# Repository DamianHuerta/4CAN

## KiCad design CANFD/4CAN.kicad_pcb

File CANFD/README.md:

# 4CAN-FD Design Files

-----------------------------------------------------------------------------------

## Note: Upon opening the project in KiCad, there may be some warnings.Click through the warnings to view the PCB as inteded.

------------------------------------------------------------------------------------

The files present in this repo are the project files used with the update of 4CAN to support CAN-FD protocol. For details on updated hardware view the Bill of Materials. All parts are available on digikey.

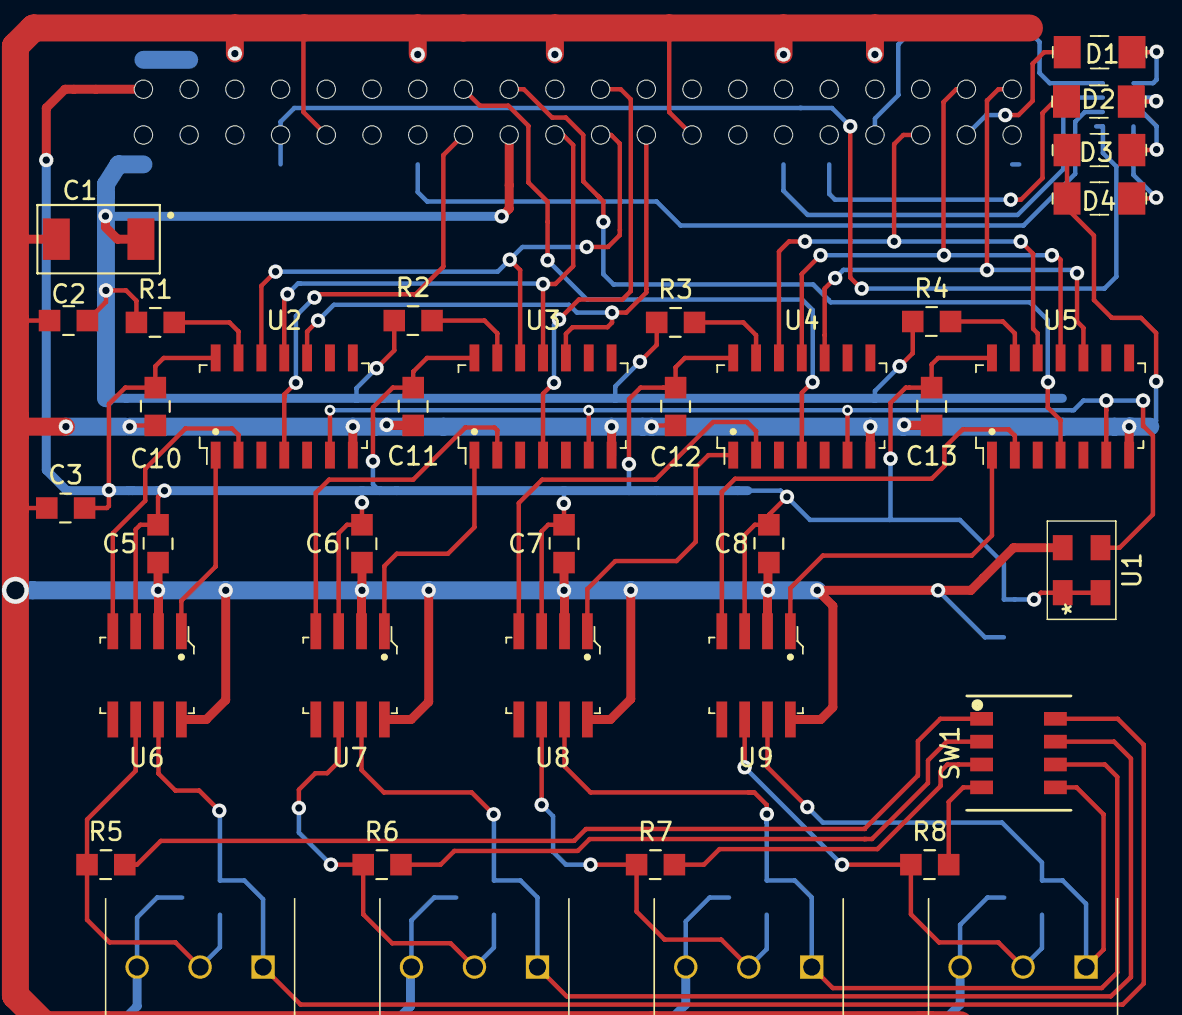
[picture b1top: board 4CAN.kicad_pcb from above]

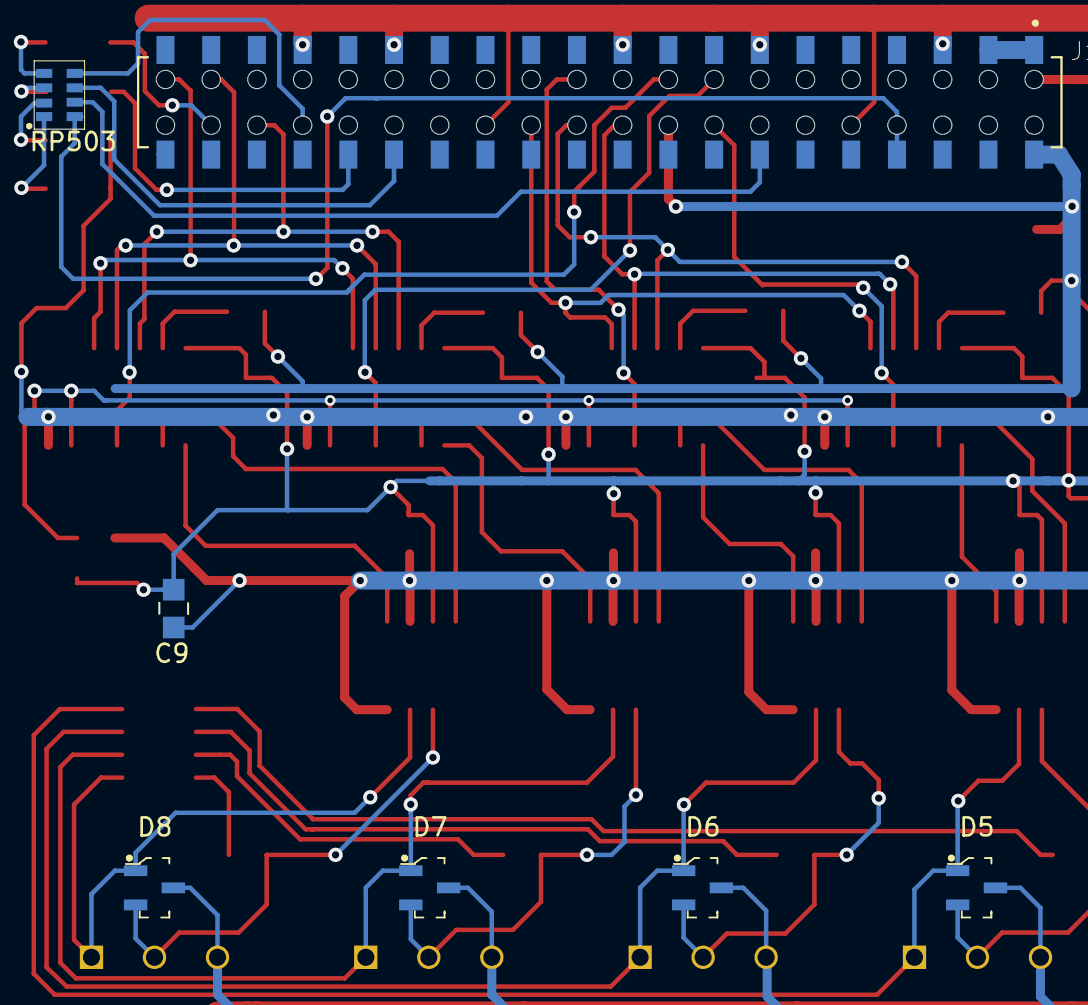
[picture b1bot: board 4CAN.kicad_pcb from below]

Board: 2 copper layers, 44 parts (7 on the bottom side), 24 nets.

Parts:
 : RP503; 742C083391JP
C1: F930J227MCC
C2, C3, C5, C6, C7, C8, C9, C10, C11, C12, C13: 0805
D1: 1206
D2, D3, D4: .; 1206
D5, D6, D7, D8: SOT-23-3
J1: SULLINS_NPTC202KFMS-RC
J2, J3, J4, J5: ED555
R1, R2, R3, R4, R5, R6, R7, R8: 0805
SW1: 218-4LPSTJ
U1: KC5032A40.0000CMGE00
U2, U3, U4, U5: SOIC-14_W3.9mm
U6, U7, U8, U9: SOIC-8_W3.9mm

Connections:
/SPI-MISO: J1.21, J1.35, J1.None, U2.12, U3.12, U4.12, U5.12
/SPI-MOSI: J1.19, U2.11, U3.11
/SPI-SCLK: J1.23, U2.10, U3.10, U4.10, U5.10
GND: C1.2, C2.2, C3.1, C5.2, C6.2, C7.2, C8.2, C9.2, C10.2, C11.2, C12.2, C13.2, D3.1, D4.1, D5.3, D6.3, D7.3, D8.3, J1.6, J1.9, J1.12, J1.14, J1.15, J1.16, J1.20, J1.22, J1.24, J1.25, J1.26, J1.30, J1.34, J1.38, J1.39, J2.3, J3.3, J4.3, J5.3, R1.2, R2.2, R3.2, U1.2, U2.7, U2.13, U3.7, U3.13, U4.7, U4.11, U4.13, U5.7, U5.11, U6.2, U6.8, U7.2, U7.8, U8.2, U8.8, U9.2, U9.8
unnamed: D5.1, D5.2, J2.1, J2.2, R5.1, SW1.8, U6.6, U6.7
unnamed: D6.1, D6.2, J3.1, J3.2, R6.1, SW1.7, U7.6, U7.7
unnamed: D7.1, D7.2, J4.1, J4.2, R7.1, SW1.6, U8.6, U8.7
unnamed: D8.1, D8.2, J5.1, J5.2, R8.1, SW1.5, U9.6, U9.7
unnamed: .8, J1.7
unnamed: J1.11, R4.2, U5.13
unnamed: R5.2, SW1.1
unnamed: R6.2, SW1.2
unnamed: R7.2, SW1.3
unnamed: R8.2, SW1.4
unnamed: U1.3, U2.6, U3.6, U4.6, U5.6
unnamed: U2.1, U6.1
unnamed: U2.2, U6.4
unnamed: U3.1, U7.1
unnamed: U3.2, U7.4
unnamed: U4.1, U8.1
unnamed: U4.2, U8.4
unnamed: U5.1, U9.1
unnamed: U5.2, U9.4
VCC: C1.1, C2.1, C3.2, C5.1, C6.1, C7.1, C8.1, C9.1, C10.1, C11.1, C12.1, C13.1, J1.1, J1.2, J1.3, J1.4, J1.17, R1.1, R2.1, R3.1, R4.1, U1.1, U1.4, U2.14, U3.14, U4.14, U5.14, U6.3, U7.3, U8.3, U9.3

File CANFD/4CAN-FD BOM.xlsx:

Description | Reference | Identifier | Quantity
220uf 6.3v tan | F930J227MCC | C1 | 1
.1uf | CC0805ZRY5V9BB104 | C2,C3,C5, C6, C7, C8, C9, C10, C11, C12, C13, | 11
Bi color LED | XZMDKVG55W-4 | D1, D2, D3, D4 | 4
CAN diode | PEGD1CAN.215 | D5, D6, D7, D8 | 4
390 Ohm | 742C083391JP | RP503A1, RP503B1, RP503C1, RP503D1 | 1
40 Mhz osc | KC5032A40.0000CMGE00 | U1 | 1
CAN FD Ctrl | MCP2518FD | U2, U3, U4, U5 | 4
CANFD Transceiver | MCP2558FD-H/SN | U6, U7, U8, U9 | 4
4 pos dip switch | 218-4LPSTJ | SW1 | 1
10k | RC805JR-0710kL | R1,R2,R3,R4 | 4
120 Ohm | RC0805FR-07120RL | R5,R6,R7,R8 | 4
40 Pin header female | NPTC202KFMS-RC | J1 | 1
3 contact scew term | ED555/XDS | J2, J3, J4, J5 | 4
40 pin male header | TSW-123-07-F-D | J6 | 1

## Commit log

2020-07-22 These files include the PCB and Schematic for an updated version of 4CAN that can utilize CANFD
2020-08-07 latest version of 4CAN-FD design files
2020-08-07 fixing README file
